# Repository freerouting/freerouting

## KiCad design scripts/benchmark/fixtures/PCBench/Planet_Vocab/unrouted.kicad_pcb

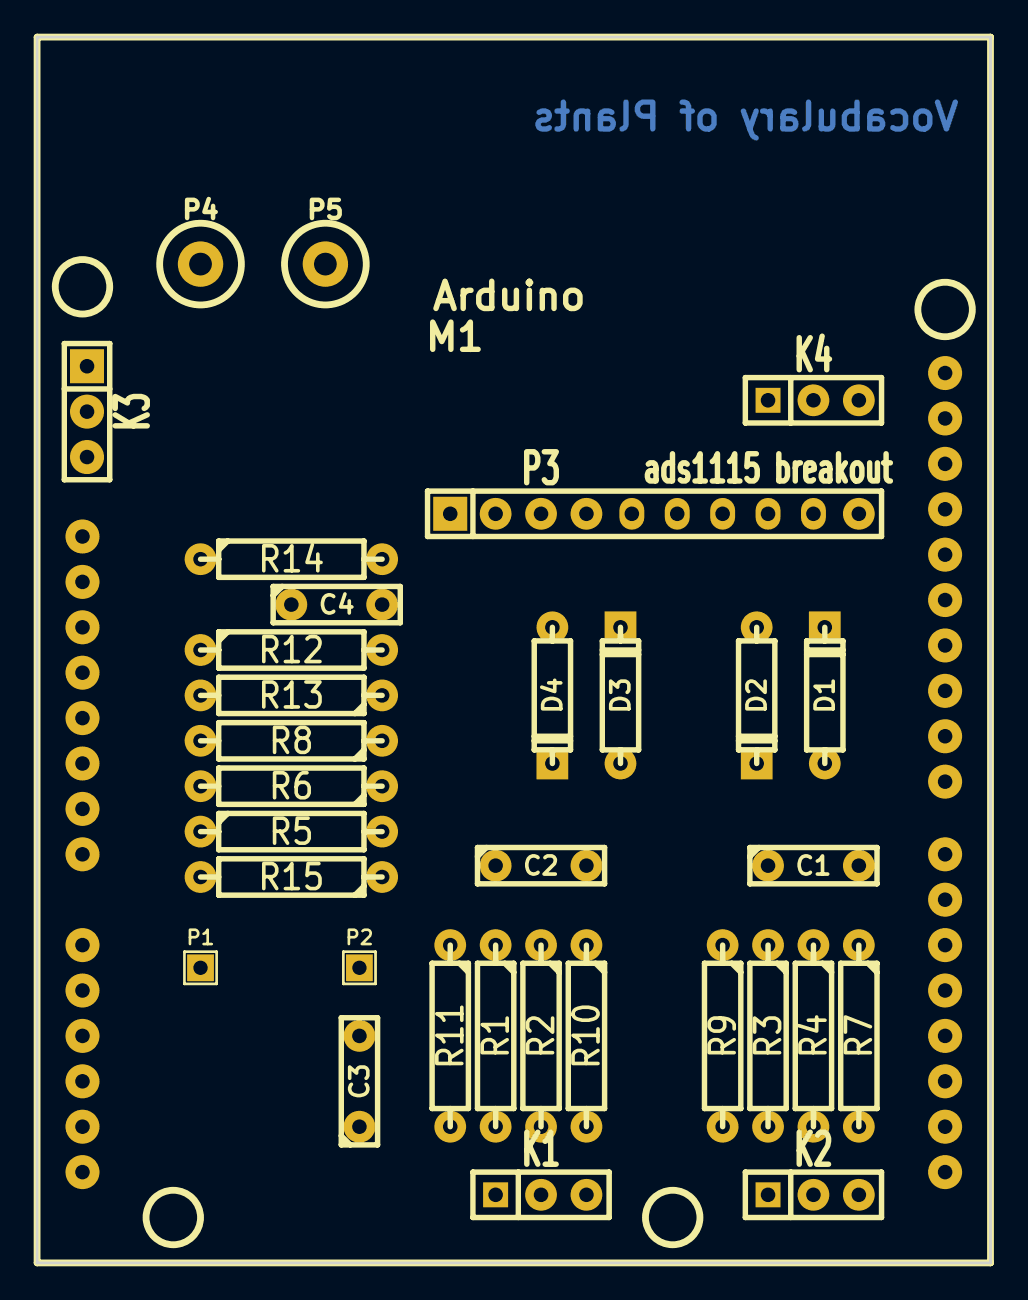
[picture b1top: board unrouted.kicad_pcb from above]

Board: 2 copper layers, 53.3 x 68.6 mm, 33 parts (0 on the bottom side), 21 nets, no tracks yet.

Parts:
C1, C2: 100n; C2
C3, C4: 10u; C2
D1, D2, D3, D4: 1n914; D3
K1, K2, K3, K4: CONN_3; SIL-3
M1: Arduino
P1, P2: CONN_1; SIL-1
P3: ads1115 breakout; SIL-10
P4, P5: CONN_1; 1pin
R1, R2, R3, R4: 100K; R4-LARGE_PADS
R5, R12, R13, R15: 10k; R4-LARGE_PADS
R6: 100k; R4-LARGE_PADS
R7, R8, R9, R10, R11: 1M; R4-LARGE_PADS
R14: 0R; R4-LARGE_PADS

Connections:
+5V: K3.3, M1.3, R12.1, R14.1
GND: C3.2, C4.2, K3.1, M1.4, M1.5, P3.2, P4.1, P5.1, R8.2, R13.2
unnamed: C2.1, D3.1, D4.2, P3.7, R1.1, R11.1
unnamed: M1.12, P3.3
unnamed: M1.11, P3.4
unnamed: C4.1, P3.1, R14.2
unnamed: M1.10, R15.2
unnamed: K4.2, P3.6
unnamed: P2.1, R6.1, R8.1
unnamed: P1.1, R5.1, R6.2
unnamed: K4.1, M1.15
unnamed: K4.3, M1.16
unnamed: K3.2, P3.5
unnamed: C2.2, D3.2, D4.1, P3.8, R2.1, R10.1
unnamed: K1.1, R1.2
unnamed: K1.2, R2.2
unnamed: K2.1, R3.2
unnamed: K2.2, R4.2
unnamed: C3.1, K1.3, K2.3, R5.2, R7.2, R9.2, R10.2, R11.2, R12.2, R13.1, R15.1
unnamed: C1.1, D1.1, D2.2, P3.9, R3.1, R9.1
unnamed: C1.2, D1.2, D2.1, P3.10, R4.1, R7.1

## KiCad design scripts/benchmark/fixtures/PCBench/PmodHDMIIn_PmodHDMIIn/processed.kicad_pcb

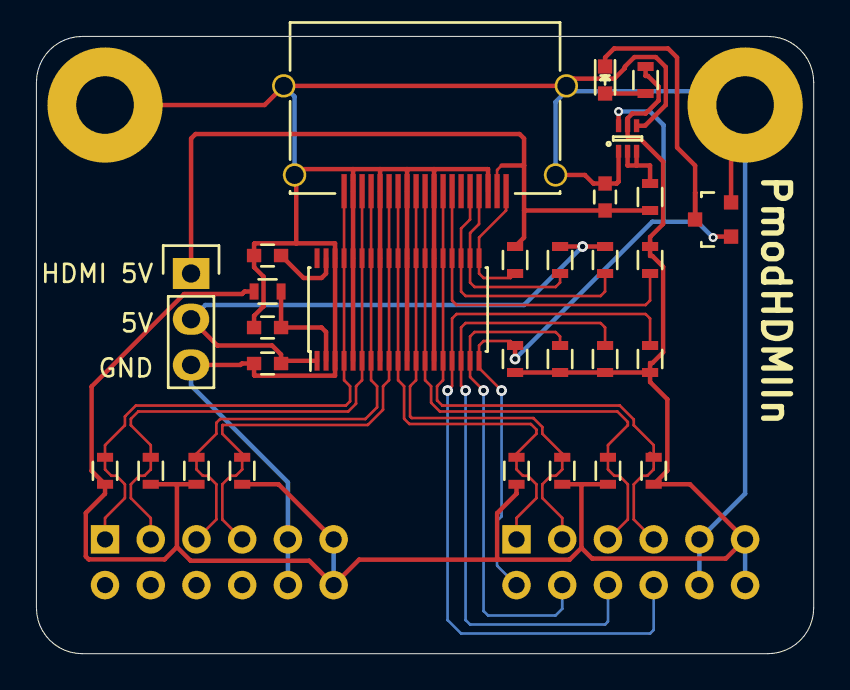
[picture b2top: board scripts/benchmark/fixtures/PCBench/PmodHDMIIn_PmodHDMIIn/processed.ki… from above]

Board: 2 copper layers, 43.2 x 34.3 mm, 33 parts (0 on the bottom side), 25 nets.

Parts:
C1, C2, C3: 100n; C_0603
C4: 0u1; C_0603
D1: LED; LED_0603
IC1: TPD12S520DBT; TSSOP-38_4.4x9.7mm_Pitch0.5mm
P1, P2: PMOD; PMOD-DUAL-MALE
P3: HDMI-A; 10029449-11xRLF
P4: POWER; Pin_Header_Straight_1x03
Q1: FDY3000NZ; SOT-563F
Q2: BSS123; SOT-23
R1, R2, R3, R4, R5, R6, R7, R8: 50R; R_0603
R9, R19: 100k; R_0603
R10: 27k; R_0603
R11, R12, R15, R17, R18: 47k; R_0603
R13: 1k; R_0603
R14: 150; R_0603
R16: 10k; R_0603
W1, W2: GND; MountingHole_3-2mm_M3_Pad

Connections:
+3V3: P1.6, P1.12, P2.6, P2.12, Q1.5, R1.1, R2.2, R3.1, R4.2, R5.1, R6.2, R7.1, R8.2, R10.1, R14.1, R15.2, R16.2, R17.2, R18.2, R19.2
+5V: C3.1, IC1.1, P4.2, R11.1, R12.1
/CEC: IC1.16, P2.10, R19.1
/CEC_HDMI: IC1.23, P3.13, R10.2
/HDMI_A_5V: C4.1, P3.18, P4.1, R9.1, R13.1
/HP: IC1.19, P2.7, Q1.6, Q2.1, R15.1
/HP_HDMI: IC1.20, P3.19, R13.2
/SCL: IC1.17, P2.9, R18.1
/SCL_HDMI: IC1.22, P3.15, R11.2
/SDA: IC1.18, P2.8, R17.1
/SDA_HDMI: IC1.21, P3.16, R12.2
/TMDS_0_N: IC1.12, IC1.27, P2.2, P3.9, R6.1
/TMDS_0_P: IC1.10, IC1.29, P2.1, P3.7, R5.2
/TMDS_1_N: IC1.9, IC1.30, P1.4, P3.6, R4.1
/TMDS_1_P: IC1.7, IC1.32, P1.3, P3.4, R3.2
/TMDS_2_N: IC1.6, IC1.33, P1.2, P3.3, R2.1
/TMDS_2_P: IC1.4, IC1.35, P1.1, P3.1, R1.2
/TMDS_C_N: IC1.15, IC1.24, P2.4, P3.12, R8.1
/TMDS_C_P: IC1.13, IC1.26, P2.3, P3.10, R7.2
GND: C1.1, C2.2, C3.2, C4.2, IC1.3, IC1.5, IC1.8, IC1.11, IC1.14, IC1.25, IC1.28, IC1.31, IC1.34, IC1.36, P1.5, P1.11, P2.5, P2.11, P3.2, P3.5, P3.8, P3.11, P3.17, P3.F1, P3.F2, P3.F3, P3.F4, P4.3, Q1.1, Q1.4, Q2.2, W1.1, W2.1
unnamed: C1.2, IC1.37
unnamed: C2.1, IC1.2, R16.1
unnamed: D1.1, Q2.3
unnamed: D1.2, R14.2
unnamed: Q1.2, Q1.3, R9.2

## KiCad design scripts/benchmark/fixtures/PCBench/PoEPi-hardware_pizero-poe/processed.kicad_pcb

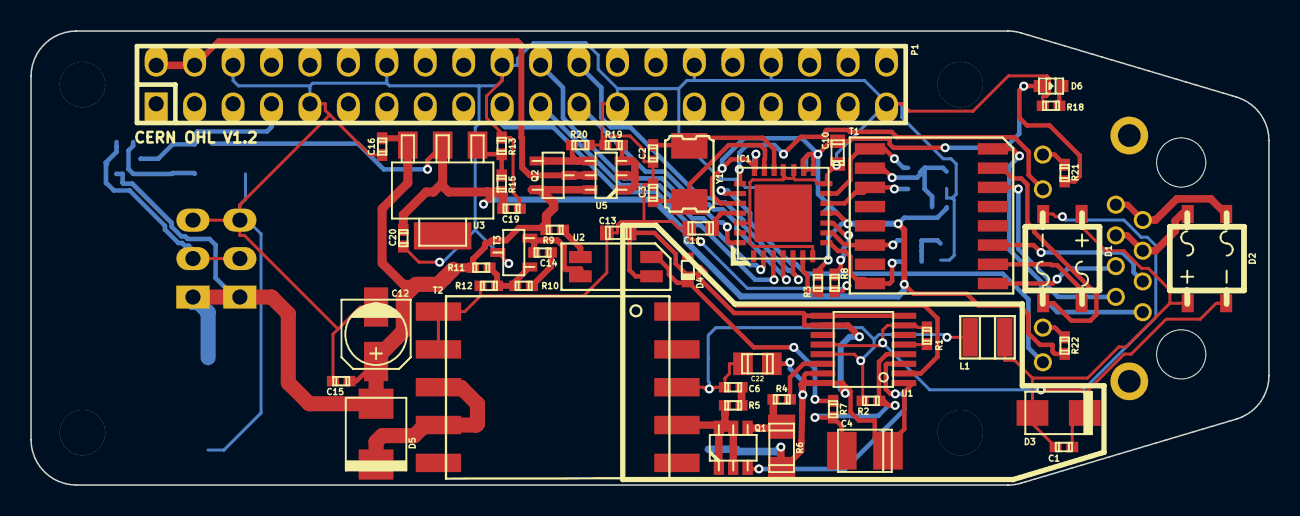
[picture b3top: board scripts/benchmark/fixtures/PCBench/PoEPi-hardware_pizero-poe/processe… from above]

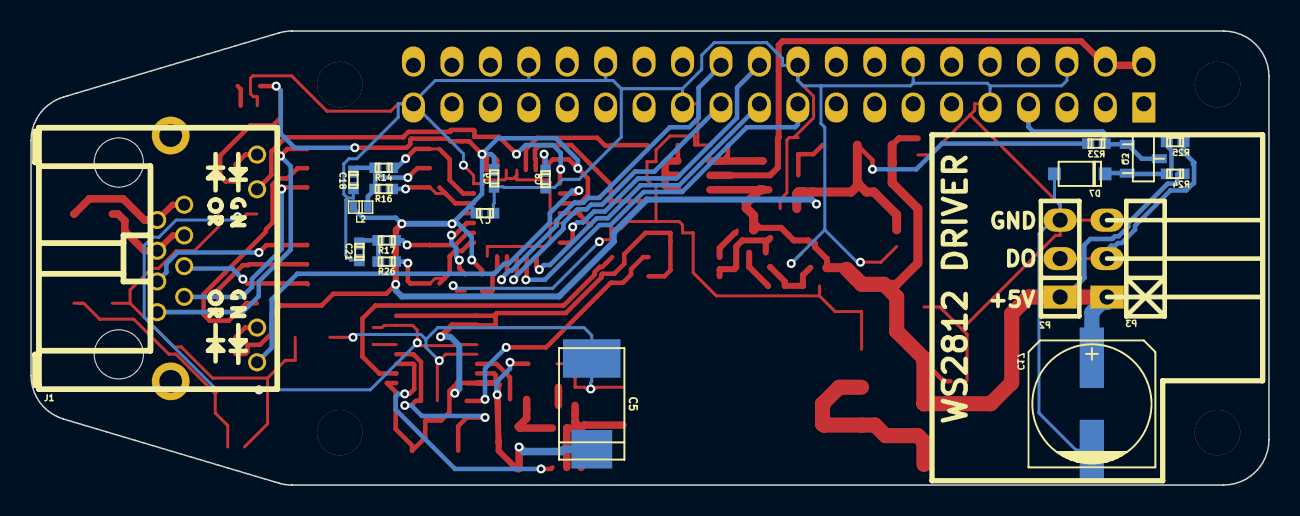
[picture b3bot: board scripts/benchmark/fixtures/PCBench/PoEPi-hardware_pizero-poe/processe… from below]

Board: 2 copper layers, 81.8 x 30.0 mm, 77 parts (20 on the bottom side), 57 nets.

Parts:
C1, C7, C8, C9, C18, C19, C21: 0.1uf; c_0402
C2, C3: 16pf; c_0402
C4: 220uf; c_tant_B
C5: 6.8uf; c_tant_D
C6, C14, C15, C16: C; c_0402
C10: 0.1uf; c_0603
C11: 10uf; c_0603
C12: CP; c_elec_4x4.5
C13: 2nf; c_0603
C17: CP; c_elec_8x6.5
C20: 1uf; c_0402
C22: 1uf; c_0805
D1, D2: BRIDGE; MBS
D3: ZENER; do214ac
D4: BAS516; sod523
D5: D_Schottky; do214aa
D6: LED; Led_0603
D7: ZENER; sod123
IC1: ENC28J60-I/ML; qfn-28
J1: RJ45-LED; rj45-tyco-2-406549-7
L1: 2.2uH; inductor_smd_1008
L2: BEAD; inductor_smd_0402
MT1, MT2, MT3, MT4: MountingHole_3mm
P1: Raspberry_Pi_+_Conn; pin_socket_20x2
P2: WS2812 Cn.; pin_strip_3
P3: WS2812 Cn.; pin_strip_3-90
Q1: SI3440DV; tsot-6
Q2, Q3: BSS138; sot23
R1: 68.1; r_0402
R2, R19: 10k; r_0402
R3: 1k; r_0402
R4, R5, R7, R9, R10, R11, R12: R; r_0402
R6: 0.05; r_1206
R8: 2.32k; r_0402
R13: 390; r_0402
R14, R16, R17, R26: 49.9; r_0402
R15: 240; r_0402
R18: 360; r_0402
R20: 47k; r_0402
R21, R22: 549; r_0402
R23, R24: 14k; r_0402
R25: 100; r_0402
T1: PULSE_H1197; H2019
T2: TRANSFO; PoE_TRANS
T3: VOLTAGE_REF; sot23
U1: LTC4267; ssop-16
U2: PAS291; OPTO_ISO
U3: LM1117IMPX-ADJ; sot223
U5: DMMT5401; sot23-6
Y1: 25Mhz; crystal_smd_5x3.2mm

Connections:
+3V3: C7.1, C8.1, C9.1, C10.1, C19.1, C20.1, D6.1, IC1.11, IC1.15, IC1.16, IC1.21, IC1.24, L2.2, R3.2, R15.1, R21.2, R22.2, R23.1, U3.2
+5V: C12.1, C15.1, C16.1, C17.1, D5.1, P2.1, P3.1, Q2.3, R9.1, R11.1, R24.1, U3.3, U5.6
/DATA_PAIR_1: D1.3, T1.10
/DATA_PAIR_2: D1.2, T1.15
/ENC_CS: IC1.5, P1.24
/ENC_INT: IC1.28, P1.22
/ENC_SCK: IC1.4, P1.23
/ENC_SI: IC1.3, P1.19
/ENC_SO: IC1.2, P1.21
/LEDA_CATH: IC1.23, J1.9
/LEDB_CATH: IC1.22, J1.11
/PVCC: C4.1, R2.2, R7.1, U1.4
/RUN: D4.2, R7.2, U2.4
/SPARE_PAIR_1: D2.3, J1.5, J1.6
/SPARE_PAIR_2: D2.2, J1.7, J1.8
/TPIN+: IC1.9, R17.2, T1.6
/TPIN-: IC1.8, R26.2, T1.8
/TPOUT+: IC1.13, R14.2, T1.1
/TPOUT-: IC1.12, R16.2, T1.3
/WS2812_DO: P1.7, Q3.1, Q3.2, R23.2
/sheet56B34F8B/5V_MCU: P1.2, P1.4, Q2.2, U5.5
GND: C2.1, C3.1, C7.2, C8.2, C9.2, C10.2, C11.1, C12.2, C13.1, C15.2, C16.2, C17.2, C18.1, C19.2, C20.2, C21.2, D7.1, IC1.7, IC1.14, IC1.17, IC1.18, IC1.26, P1.6, P1.9, P1.14, P1.20, P1.25, P1.30, P1.34, P1.39, P2.3, P3.3, R8.1, R12.2, R13.2, R18.2, R19.2, R20.2, T2.9, T2.10, T3.2
GNDPWR: C4.2, C5.2, C13.2, C22.2, R6.2, U1.1, U1.8, U1.9, U1.10, U1.15, U1.16, U2.3
unnamed: C1.1, D1.1, D2.1, D3.1, L1.1
unnamed: C1.2, D1.4, D2.4, D3.2, R1.2, U1.7, U1.12
unnamed: C2.2, IC1.19, Y1.1
unnamed: C3.2, IC1.20, Y1.2
unnamed: C6.2, R5.2
unnamed: C11.2, IC1.25
unnamed: C14.1, T3.3, U2.2
unnamed: C14.2, R10.2
unnamed: C18.2, L2.1, R14.1, R16.1, T1.2
unnamed: C21.1, R17.1, R26.1
unnamed: C5.1, C6.1, C22.1, L1.2, R2.1, T2.3, U1.13
unnamed: D4.1, U1.2
unnamed: D5.2, T2.7, T2.8
unnamed: D6.2, R18.1
unnamed: D7.2, Q3.3, R24.2, R25.2
unnamed: IC1.6, R3.1
unnamed: IC1.10, R8.2
unnamed: J1.1, T1.16
unnamed: J1.2, T1.14
unnamed: J1.3, T1.11
unnamed: J1.4, T1.9
unnamed: J1.10, R22.1
unnamed: J1.12, R21.1
unnamed: P2.2, P3.2, R25.1
unnamed: Q1.1, Q1.2, Q1.5, Q1.6, R5.1, T2.4
unnamed: Q1.3, U1.3
unnamed: Q1.4, R4.1, R6.1
unnamed: Q2.1, R20.1, U5.4
unnamed: R1.1, U1.5
unnamed: R4.2, U1.14
unnamed: R9.2, U2.1
unnamed: R10.1, R11.2, R12.1, T3.1
unnamed: R13.1, R15.2, U3.1
unnamed: R19.1, U5.1, U5.2, U5.3

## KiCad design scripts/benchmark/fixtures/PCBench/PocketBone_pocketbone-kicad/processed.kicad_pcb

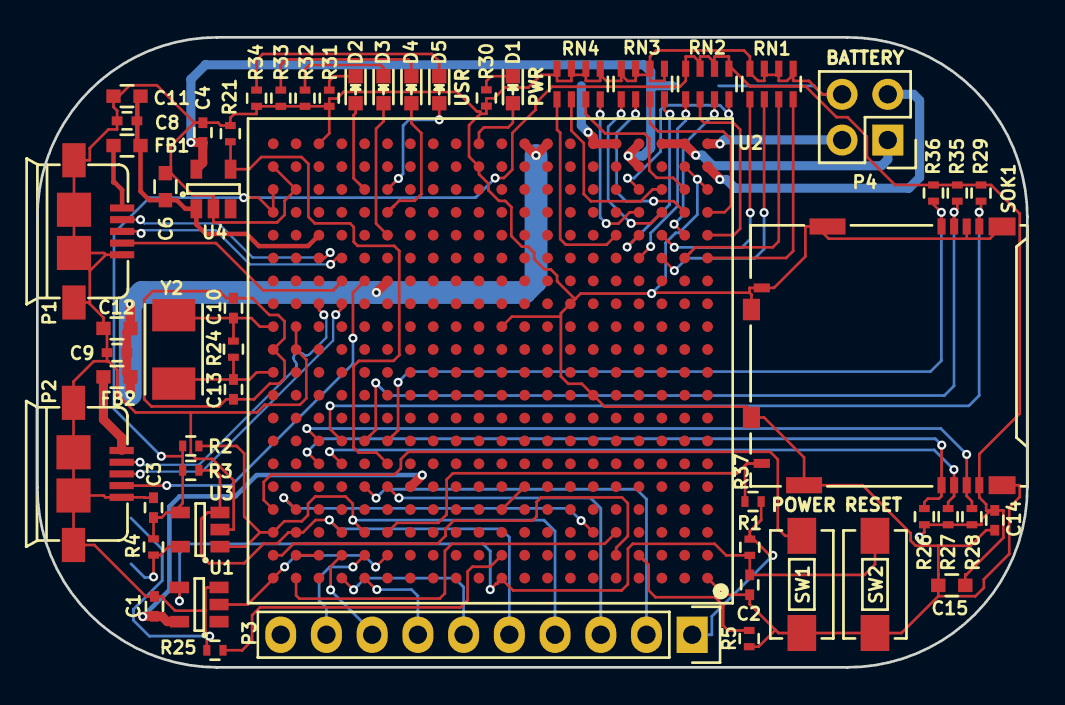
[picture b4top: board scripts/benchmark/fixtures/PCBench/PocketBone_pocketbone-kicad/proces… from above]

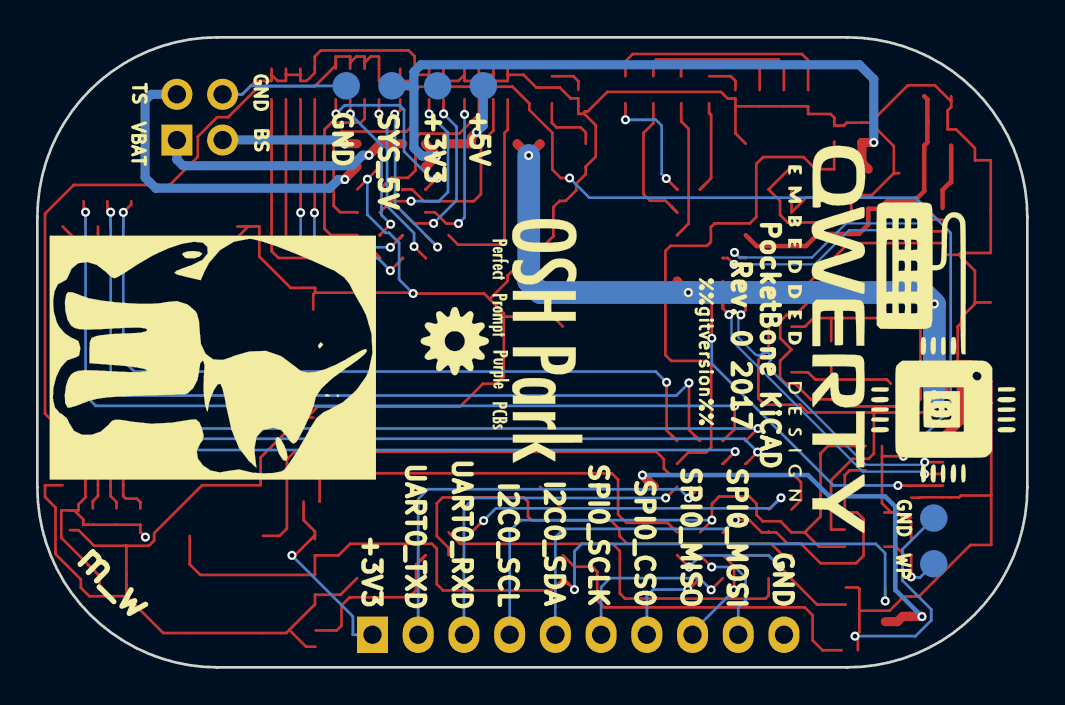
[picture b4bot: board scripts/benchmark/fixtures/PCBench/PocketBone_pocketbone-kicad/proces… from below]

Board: 4 copper layers, 55.0 x 35.0 mm, 62 parts (6 on the bottom side), 74 nets.

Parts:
C1, C3, C4, C8, C9, C14: 0.1uF; C_0402
C2: 1uF; C_0402
C6, C11, C12, C15: 10uF; C_0603
C10, C13: 18pF; C_0402
D1, D2, D3, D4, D5: BLUE; LED-0603
FB1, FB2: FILTER; C_0603
P1, P2: USB_OTG; USB_MICRO_B_ST-USB-001E
P3: CONN_01X10; Socket_Strip_Straight_1x10
P4: CONN_02X02; Socket_Strip_Straight_2x02
R1, R5, R26, R27, R28, R29, R35, R36, R37: 10K; R_0402
R2, R3, R4: 1.5K; R_0402
R21: 100K; R_0402
R24: 1M; R_0402
R25: 4.87K; R_0402
R30: 4.7K; R_0402
R31, R32, R33, R34: 240; R_0402
RN1, RN2, RN3, RN4: 100K; R_Array_Concave_4x0603
SOK1: SCHA5B0200
SW1, SW2: SW_PUSH_SMALL_H; SW_SPST_EVQPE1
TP1: 5V; Measurement_Point_Round-SMD-Pad_Small
TP2: WP; Measurement_Point_Round-SMD-Pad_Small
TP3, TP6: GND; Measurement_Point_Round-SMD-Pad_Small
TP4: 3P3; Measurement_Point_Round-SMD-Pad_Small
TP5: SYS_5V; Measurement_Point_Round-SMD-Pad_Small
U1: SN74LVC1G07; SOT-23-5
U2: OSD3358; BGA-400-1-27mm
U3: 24LC32AT-I/OT; SOT-23-5
U4: TPS2051C; SOT-23-5
Y2: 24MHz; 445C33D24M00000

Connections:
3P3AUX: D1.2, U2.Y11
+3V3: C3.1, C14.1, C15.1, P3.1, R1.1, R2.1, R3.1, R4.1, R26.1, R27.1, R28.1, R29.1, R35.1, R36.1, R37.1, RN2.5, RN2.6, RN2.7, RN2.8, SOK1.4, U2.U20, U2.V20, U3.4
+5V: TP1.1, U2.Y5, U2.Y6
BAT_SENSE: P4.3, U2.Y1
GND: C1.2, C2.2, C3.2, C4.2, C6.2, C8.2, C9.2, C11.2, C12.2, C14.2, C15.2, P1.5, P1.6, P1.7, P1.8, P1.9, P2.5, P2.6, P2.7, P2.8, P2.9, P3.10, P4.4, R5.2, R21.2, R25.1, R30.1, R31.1, R32.1, R33.1, R34.1, RN1.1, RN1.2, RN1.3, RN1.4, RN3.1, RN3.2, RN3.3, RN3.4, RN4.1, RN4.2, RN4.3, RN4.4, SOK1.6, SOK1.10, SOK1.11, SW1.1, SW2.1, TP3.1, TP6.1, U1.3, U2.A1, U2.J6, U2.L19, U2.M10, U2.M19, U2.N7, U2.V1, U2.V19, U2.W2, U2.W11, U2.W20, U2.Y18, U3.2, U4.2
I2C0_SCL: P3.4, R2.2, U2.C16, U2.C20, U3.1
I2C0_SDA: P3.5, R3.2, U2.C17, U2.C19, U3.3
MMC0_CD: R37.2, SOK1.9, U2.C15
MMC0_CLK: R29.2, SOK1.5, U2.G17
MMC0_CMD: R28.2, SOK1.3, U2.G18
MMC0_DAT0: R35.2, SOK1.7, U2.G16
MMC0_DAT1: R36.2, SOK1.8, U2.G15
MMC0_DAT2: R26.2, SOK1.1, U2.F18
MMC0_DAT3: R27.2, SOK1.2, U2.F17
unnamed: C2.1, R1.2, SW2.2, U1.4, U2.A10
unnamed: C10.1, R24.2, U2.M20, Y2.1
unnamed: C13.1, R24.1, U2.K20, Y2.2
unnamed: D1.1, R30.2
unnamed: D2.1, R31.2
unnamed: D3.1, R32.2
unnamed: D4.1, R33.2
unnamed: D5.1, R34.2
unnamed: FB1.2, P1.1
unnamed: FB2.2, P2.1
unnamed: R4.2, TP2.1, U3.5
unnamed: R5.1, U2.B4
unnamed: RN1.5, U2.T3
unnamed: RN1.6, U2.R3
unnamed: RN1.7, U2.R2
unnamed: RN1.8, U2.R1
unnamed: RN2.1, U2.R4
unnamed: RN2.2, U2.T1
unnamed: RN2.3, U2.T2
unnamed: RN2.4, U2.V4
unnamed: RN3.5, U2.U3
unnamed: RN3.6, U2.U2
unnamed: RN3.7, U2.U1
unnamed: RN3.8, U2.T4
unnamed: RN4.5, U2.T5
unnamed: RN4.6, U2.V3
unnamed: RN4.7, U2.V2
unnamed: RN4.8, U2.U4
unnamed: SW1.2, U2.D20
unnamed: U2.A19, U2.C5
unnamed: U2.B18, U2.B19
unnamed: U2.B5, U2.B20
unnamed: U2.C6, U2.D19
OSC0_GND: C10.2, C13.2, U2.L20
PMIC_PGOOD: U1.2, U2.A20, U2.B15
SPI_CLK: P3.6, U2.A17
SPI_CS0: P3.7, U2.A16
SPI_MISO: P3.8, U2.B17
SPI_MOSI: P3.9, U2.B16
SYS_5V: C4.1, TP5.1, U2.W4, U2.Y4, U4.5
TRSTN: R25.2, U2.B10
TS: P4.2, U2.W1
UART0_RXD: P3.3, U2.E15
UART0_TXD: P3.2, U2.E16
USB0_D_N: P2.2, U2.N18
USB0_D_P: P2.3, U2.N17
USB0_ID: P2.4, U2.P16
USB0_VBUS: C9.1, C12.1, FB2.1, U2.P15, U2.Y8, U2.Y9
USB1_DRVVBUS: R21.1, U2.F15, U4.4
USB1_D_N: P1.2, U2.R18
USB1_D_P: P1.3, U2.R17
USB1_ID: P1.4, U2.P17
USB1_VBUS: C6.1, C8.1, C11.1, FB1.1, U2.T18, U4.1
USR0_LED: D5.2, U2.V15
USR1_LED: D4.2, U2.U15
USR2_LED: D3.2, U2.T15
USR3_LED: D2.2, U2.V16
VBAT: P4.1, U2.Y2, U2.Y3
VDD_1V8: U2.D10, U2.E9
VDD_RTC: C1.1, U1.5, U2.E14

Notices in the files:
scripts/benchmark/fixtures/PCBench/PmodHDMIIn_PmodHDMIIn/processed.kicad_pcb:
License: CC BY-SA 4.0
scripts/benchmark/fixtures/PCBench/PoEPi-hardware_pizero-poe/processed.kicad_pcb:
License: CERN OHL V1.2
CERN OHL V1.2
